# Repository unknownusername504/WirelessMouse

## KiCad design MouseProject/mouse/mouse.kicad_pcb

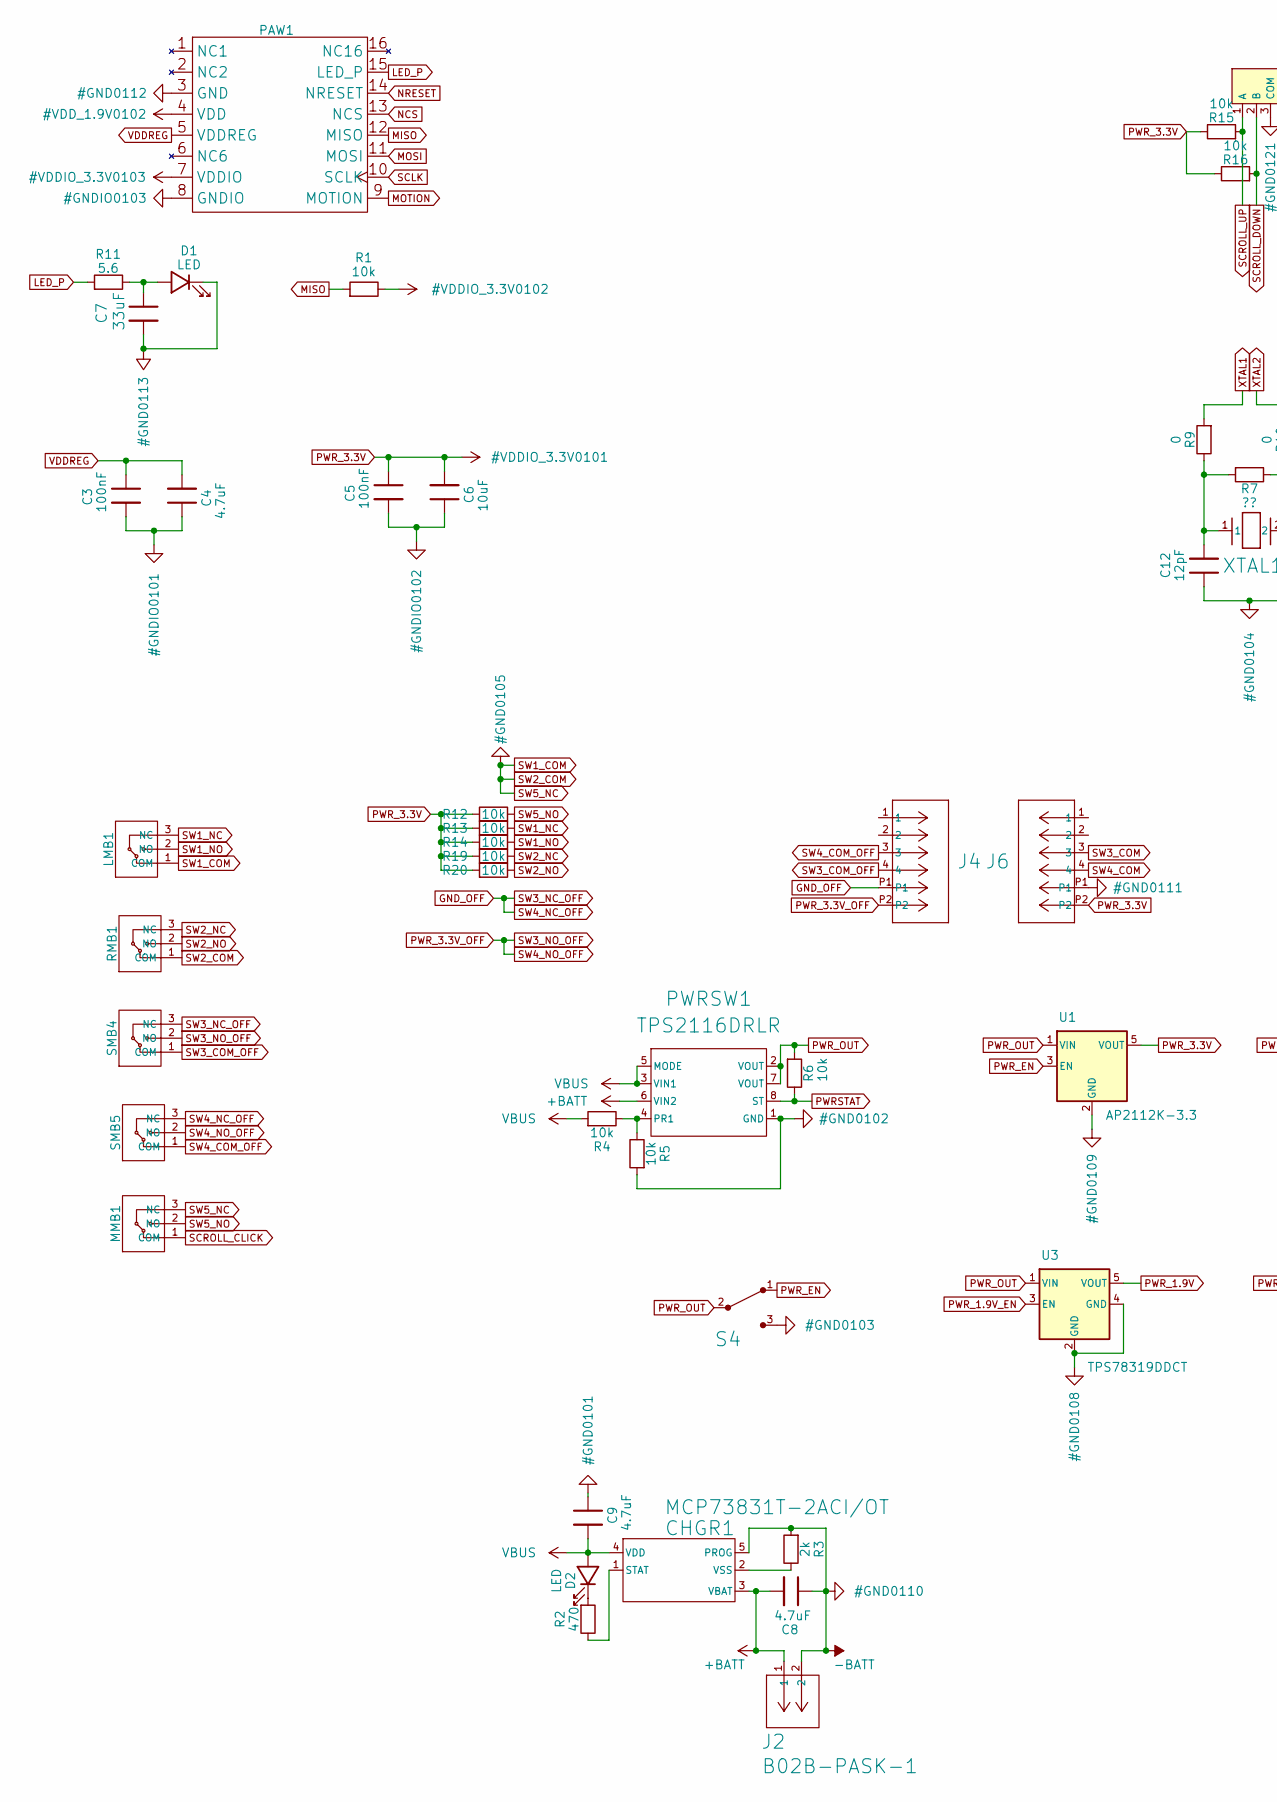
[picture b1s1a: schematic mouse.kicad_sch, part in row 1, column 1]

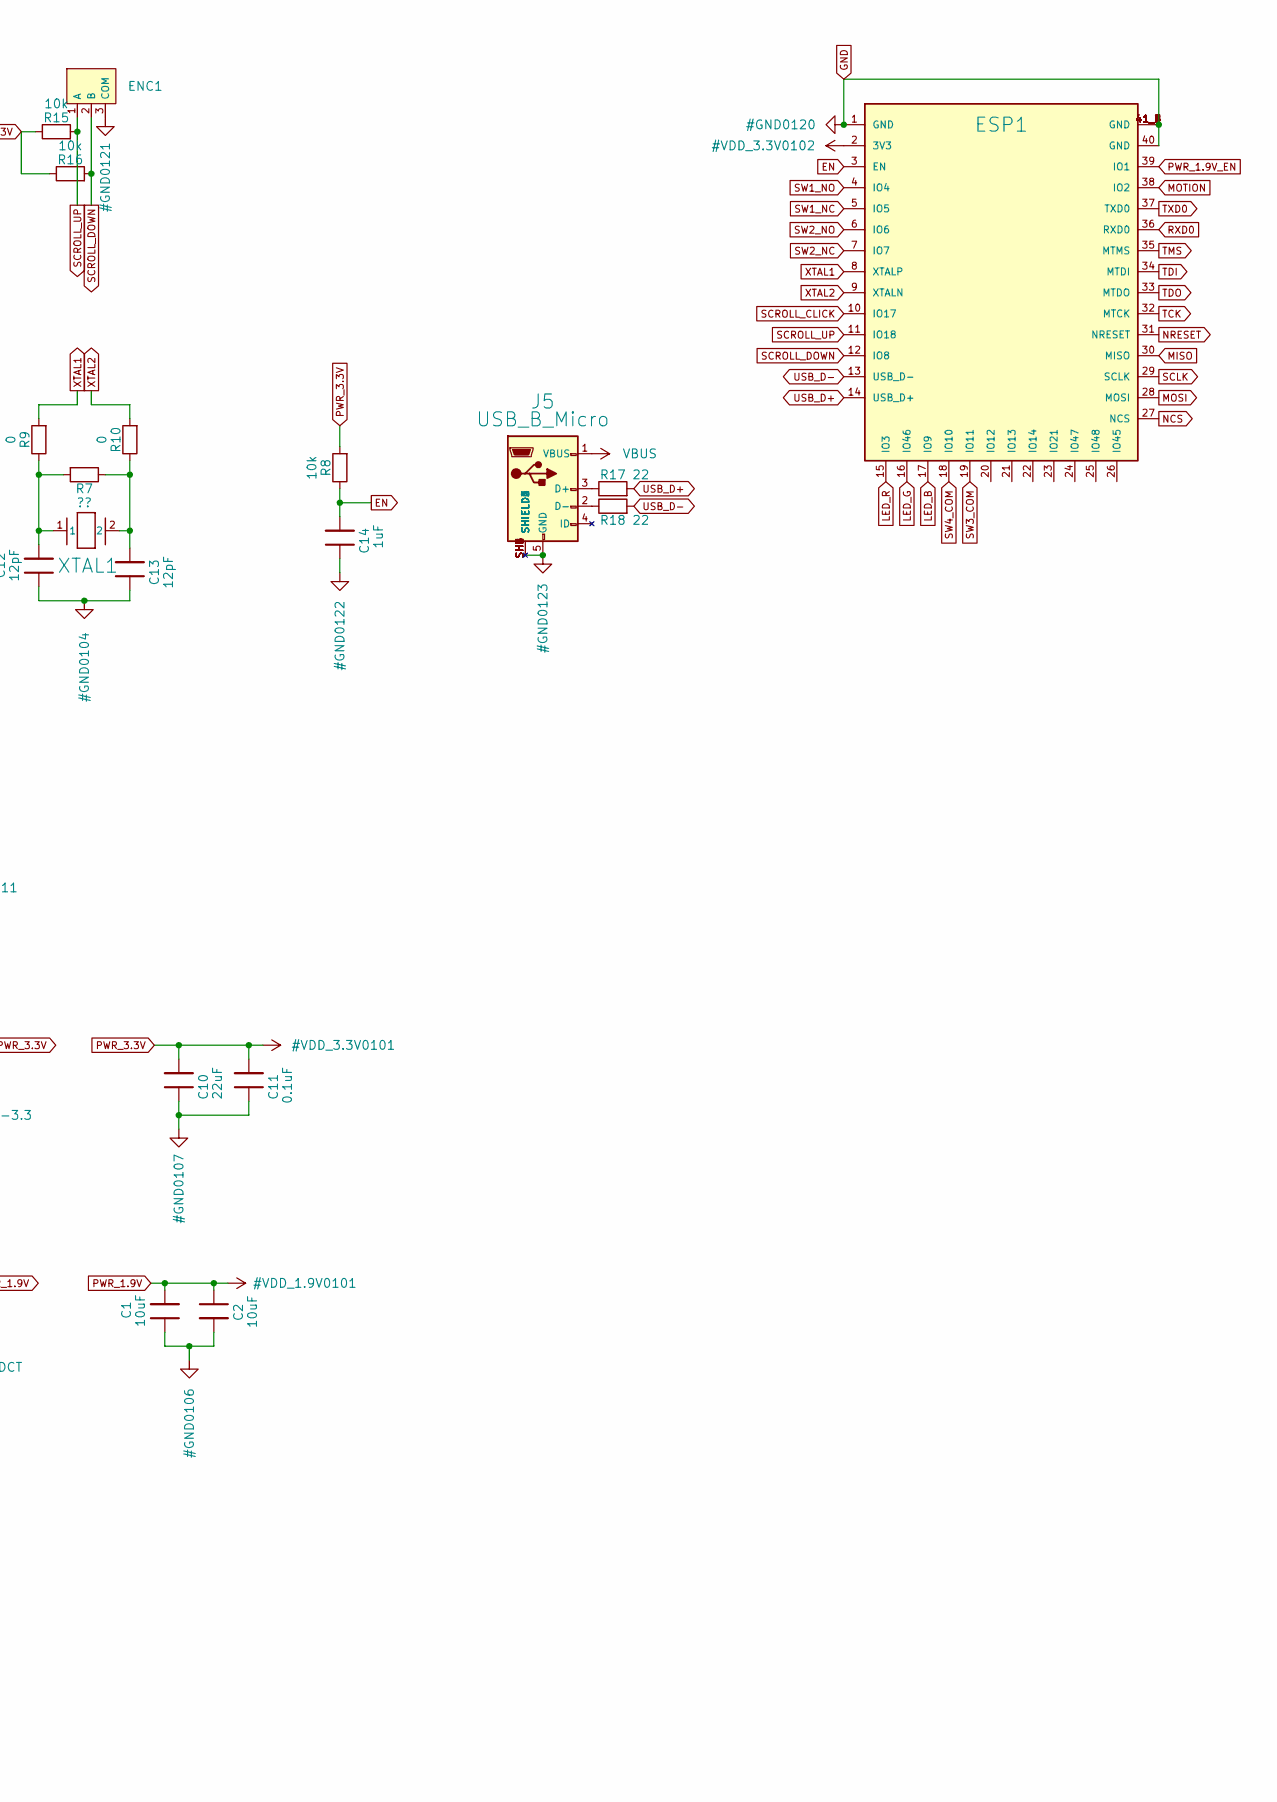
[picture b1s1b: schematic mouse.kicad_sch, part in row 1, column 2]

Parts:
C1, C2, C6: 10uF; C_0201_0603Metric
C3, C5: 100nF; C_0201_0603Metric
C4, C8, C9: 4.7uF; C_0201_0603Metric
C7: 33uF; C_0201_0603Metric
C10: 22uF; C_0201_0603Metric
C11: 0.1uF; C_0201_0603Metric
C12, C13: 12pF; C_0201_0603Metric
C14: 1uF; C_0201_0603Metric
CHGR1: MCP73831T-2ACI/OT; SOT-23-5_MC_MCH
D1, D2: LED; LED_0201_0603Metric
ENC1: TTC_GOLD_ENCODER
ESP1: ESP32-S3-WROOM-1U
J2: B02B-PASK-1; CONN_B02B-PASK-1_JST
J4, J6: 5051100492; CON_5051100492_MOL
J5: USB_B_Micro; MOLEX_1050170001
LMB1: KailhSw
MMB1: KailhSw
PAW1: PAW3395
PWRSW1: TPS2116DRLR; DRL0008A-MFG
R1, R4, R5, R6, R8, R12, R13, R14, R15, R16, R19, R20: 10k; R_0201_0603Metric
R2: 470; R_0201_0603Metric
R3: 2k; R_0201_0603Metric
R7: ??; R_0201_0603Metric
R9, R10: 0; R_0201_0603Metric
R11: 5.6; R_0201_0603Metric
R17, R18: 22; R_0201_0603Metric
RMB1: KailhSw
S4: EG1218; Switch_Slide_11.6x4mm_EG1218; MPN EG1218; Digi-Key_PN EG1903-ND
SMB4, SMB5: KailhSw
U1: AP2112K-3.3; SOT-23-5
U3: TPS78319DDCT; DDC5_TEX
XTAL1: RT3215-32.768-12.5-TR; RT3215_RAL

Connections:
+BATT: C8.2, CHGR1.3 (VBAT), J2.1, PWRSW1.6 (VIN2)
EN: C14.2, ESP1.3 (EN), R8.2
GND: C1.1, C2.2, C7.2, C8.1, C9.1, C10.1, C11.1, C12.1, C13.1, C14.1, CHGR1.5 (PROG), D1.1 (K), ENC1.3 (COM), ESP1.1 (GND), ESP1.40 (GND), ESP1.41_1 (GND), ESP1.41_2 (GND), ESP1.41_3 (GND), ESP1.41_4 (GND), ESP1.41_5 (GND), ESP1.41_6 (GND), ESP1.41_7 (GND), ESP1.41_8 (GND), ESP1.41_9 (GND), J2.2, J5.5 (GND), J5.SH1 (SHIELD1), J5.SH2 (SHIELD2), J5.SH3 (SHIELD3), J5.SH4 (SHIELD4), J5.SH5 (SHIELD5), J5.SH6 (SHIELD6), J6.P1, LMB1.1 (COM), MMB1.3 (NC), PAW1.3 (GND), PWRSW1.1 (GND), R3.1, R5.1, RMB1.1 (COM), S4.3, U1.2 (GND), U3.2 (GND), U3.4 (GND)
GND1: C3.2, C4.1, C5.2, C6.1, PAW1.8 (GNDIO)
GND_OFF: J4.P1, SMB4.3 (NC), SMB5.3 (NC)
LED_B: ESP1.17 (IO9)
LED_G: ESP1.16 (IO46)
LED_P: PAW1.15 (LED_P), R11.1
LED_R: ESP1.15 (IO3)
MISO: ESP1.30 (MISO), PAW1.12 (MISO), R1.1
MOSI: ESP1.28 (MOSI), PAW1.11 (MOSI)
MOTION: ESP1.38 (IO2), PAW1.9 (MOTION)
NCS: ESP1.27 (NCS), PAW1.13 (NCS)
NRESET: ESP1.31 (NRESET), PAW1.14 (NRESET)
unnamed: C12.2, R7.1, R9.2, XTAL1.1
unnamed: C13.2, R7.2, R10.2, XTAL1.2
unnamed: CHGR1.1 (STAT), R2.2
unnamed: CHGR1.2 (VSS), R3.2
unnamed: C7.1, D1.2 (A), R11.2
unnamed: D2.1 (K), R2.1
unnamed: J5.3 (D+), R17.2
unnamed: J5.2 (D-), R18.2
unnamed: PWRSW1.4 (PR1), R4.2, R5.2
PWRSTAT: PWRSW1.8 (ST), R6.2
PWR_1.9V: C1.2, C2.1, PAW1.4 (VDD), U3.5 (VOUT)
PWR_1.9V_EN: ESP1.39 (IO1), U3.3 (EN)
PWR_3.3V: C5.1, C6.2, C10.2, C11.2, ESP1.2 (3V3), J6.P2, PAW1.7 (VDDIO), R1.2, R8.1, R12.1, R13.1, R14.1, R15.2, R16.2, R19.1, R20.1, U1.5 (VOUT)
PWR_3.3V_OFF: J4.P2, SMB4.2 (NO), SMB5.2 (NO)
PWR_EN: S4.1, U1.3 (EN)
PWR_OUT: PWRSW1.2 (VOUT), PWRSW1.7 (VOUT), R6.1, S4.2, U1.1 (VIN), U3.1 (VIN)
RXD0: ESP1.36 (RXD0)
SCLK: ESP1.29 (SCLK), PAW1.10 (SCLK)
SCROLL_CLICK: ESP1.10 (IO17), MMB1.1 (COM)
SCROLL_DOWN: ENC1.2 (B), ESP1.12 (IO8), R16.1
SCROLL_UP: ENC1.1 (A), ESP1.11 (IO18), R15.1
SW1_NC: ESP1.5 (IO5), LMB1.3 (NC), R13.2
SW1_NO: ESP1.4 (IO4), LMB1.2 (NO), R14.2
SW2_NC: ESP1.7 (IO7), R19.2, RMB1.3 (NC)
SW2_NO: ESP1.6 (IO6), R20.2, RMB1.2 (NO)
SW3_COM: ESP1.19 (IO11), J6.3
SW3_COM_OFF: J4.4, SMB4.1 (COM)
SW4_COM: ESP1.18 (IO10), J6.4
SW4_COM_OFF: J4.3, SMB5.1 (COM)
SW5_NO: MMB1.2 (NO), R12.2
TCK: ESP1.32 (MTCK)
TDI: ESP1.34 (MTDI)
TDO: ESP1.33 (MTDO)
TMS: ESP1.35 (MTMS)
TXD0: ESP1.37 (TXD0)
USB_D+: ESP1.14 (USB_D+), R17.1
USB_D-: ESP1.13 (USB_D-), R18.1
VBUS: C9.2, CHGR1.4 (VDD), D2.2 (A), J5.1 (VBUS), PWRSW1.3 (VIN1), PWRSW1.5 (MODE), R4.1
VDDREG: C3.1, C4.2, PAW1.5 (VDDREG)
XTAL1: ESP1.8 (XTALP), R9.1
XTAL2: ESP1.9 (XTALN), R10.1

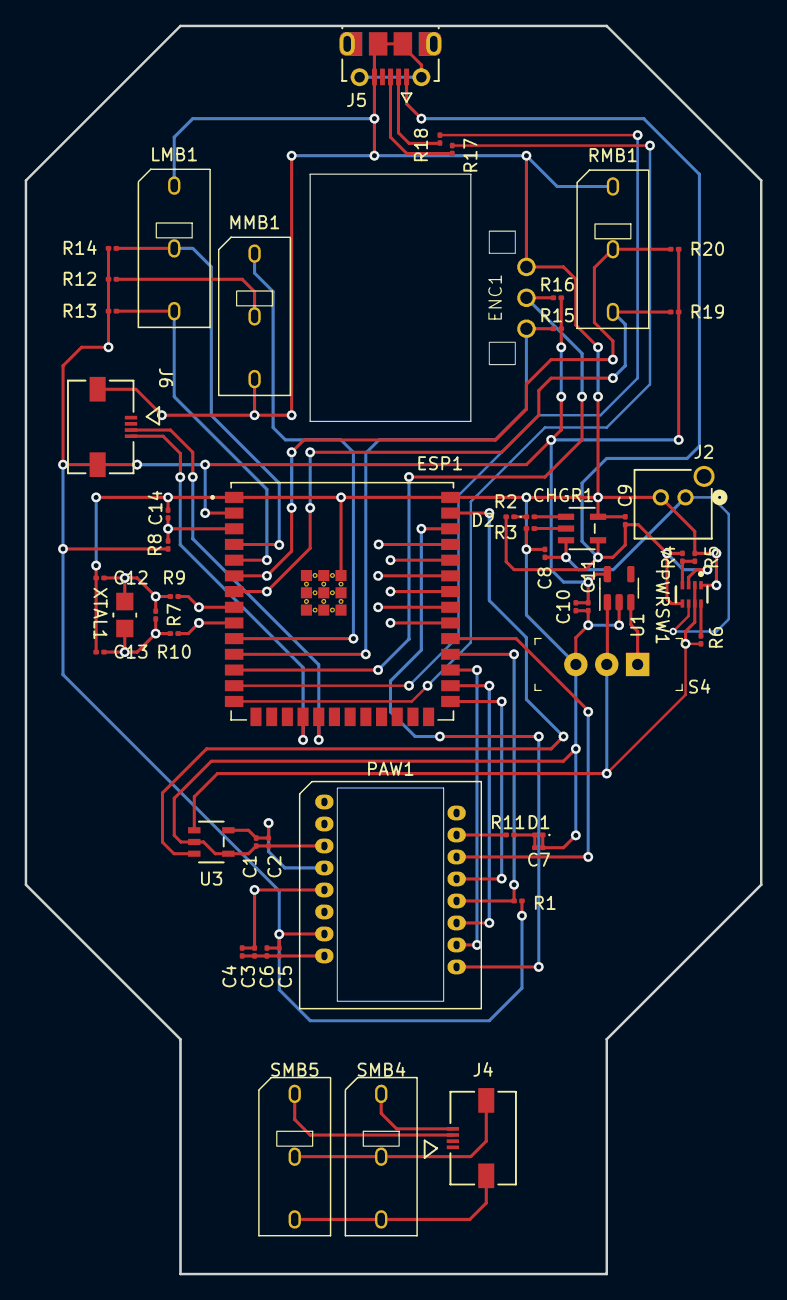
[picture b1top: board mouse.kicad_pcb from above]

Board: 2 copper layers, 59.5 x 101.0 mm, 54 parts (0 on the bottom side), 46 nets.

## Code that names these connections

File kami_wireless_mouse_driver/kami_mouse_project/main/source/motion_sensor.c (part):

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// The sensor is configured to use a 4 wire interface. (default)

// The sensor is connected to the following pins:
// NCS: GPIO_NUM_27
// MOSI: GPIO_NUM_28
// SCLK: GPIO_NUM_29
// MISO: GPIO_NUM_30
// NRESET: GPIO_NUM_31
// MOTION: GPIO_NUM_38
// PWR_EN: GPIO_NUM_39

// Set up the IO pins for the sensor.
static const gpio_config_t sensor_ncs_config = {
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
// Function to set the sensor into motion burst mode from the Pixart PAW3395 sensor.
/**
5.2 Motion Pin Timing
The motion pin is an active low output that signals the micro-controller when motion has occurred. The motion pin
is lowered whenever the motion bit is set; in other words, whenever there is non-zero data in the Delta_X_L,
Delta_X_H, Delta_Y_L or Delta_Y_H registers. Clearing the motion bit (by reading Delta_X_L, Delta_X_H, Delta_Y_L
or Delta_Y_H registers) will put the motion pin high.

5.7 Burst Mode Operation
Burst mode is a special serial port operation mode which is used to reduce the serial transaction time for
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Ensure all supplies are stable.
2. Wait for at least 50 ms.
3. Drive NCS high, and then low to reset the SPI port.
4. Write 0x5A to Power_Up_Reset register (or alternatively toggle the NRESET pin).
5. Wait for at least 5ms.
6. Load Power-up initialization register setting.
7. Read registers 0x02, 0x03, 0x04, 0x05 and 0x06 one time regardless of the motion bit state.
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    ESP_ERROR_CHECK(gpio_set_level(GPIO_NUM_27, 0));
    vTaskDelay(pdUS_TO_TICKS(SENSOR_RESET_DELAY_US));
    // Toggle the reset pin.
    // The NRESET pin needs to be asserted (held to logic 0) for at least
    // 100 ns duration for the chip to reset.
    ESP_ERROR_CHECK(gpio_set_level(GPIO_NUM_31, 1));
    vTaskDelay(pdUS_TO_TICKS(SENSOR_RESET_DELAY_US));
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
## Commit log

2023-12-04 Updates to algos for mouse
2023-12-04 Bad conversion
